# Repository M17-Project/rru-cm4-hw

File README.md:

[![CC BY-NC-SA 4.0][cc-by-nc-sa-shield]][cc-by-nc-sa]

# rru-cm4-hw
Remote Radio Unit - interface board

## License
This work is licensed under a
[Creative Commons Attribution-NonCommercial-ShareAlike 4.0 International License][cc-by-nc-sa].

[![CC BY-NC-SA 4.0][cc-by-nc-sa-image]][cc-by-nc-sa]

[cc-by-nc-sa]: http://creativecommons.org/licenses/by-nc-sa/4.0/
[cc-by-nc-sa-image]: https://licensebuttons.net/l/by-nc-sa/4.0/88x31.png
[cc-by-nc-sa-shield]: https://img.shields.io/badge/License-CC%20BY--NC--SA%204.0-lightgrey.svg

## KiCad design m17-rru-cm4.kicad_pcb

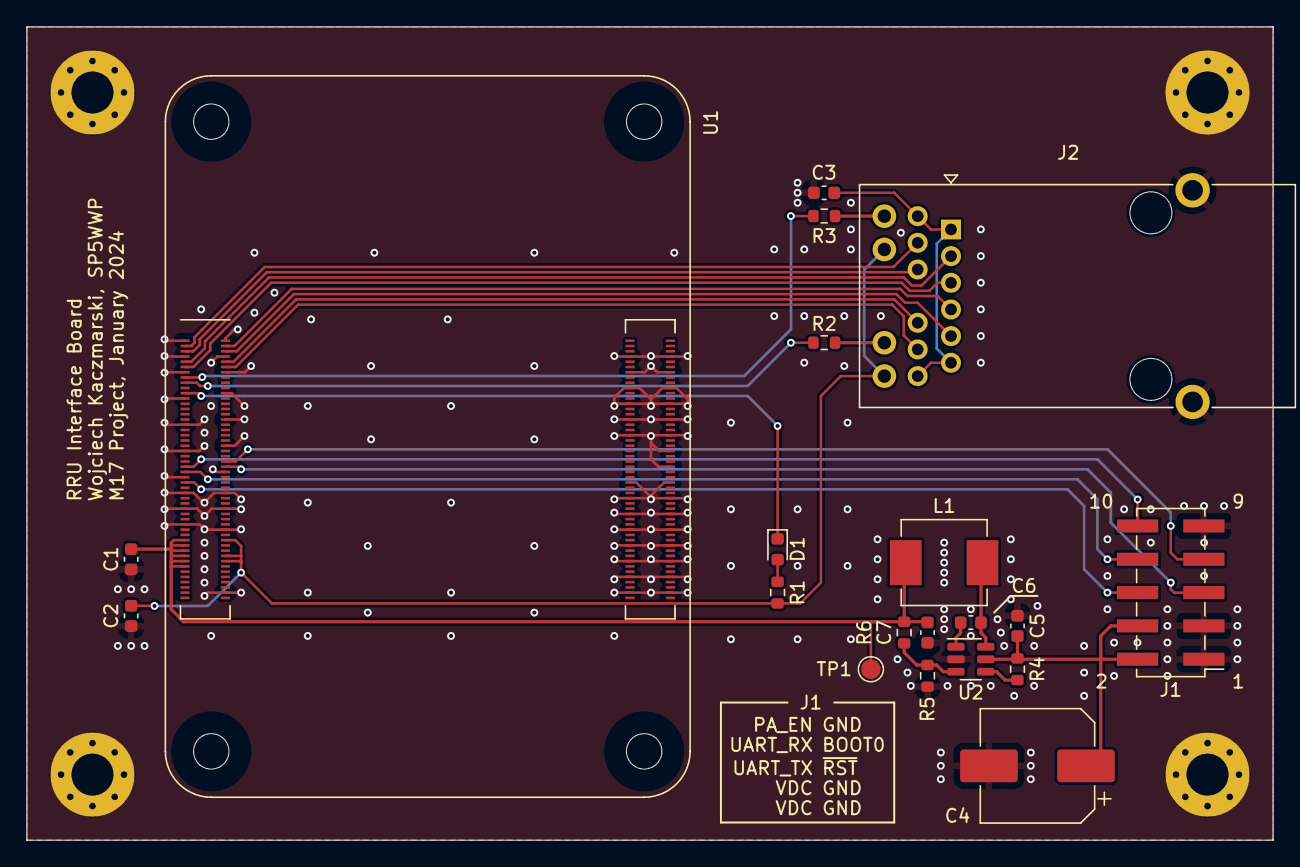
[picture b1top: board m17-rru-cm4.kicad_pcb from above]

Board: 2 copper layers, 95.0 x 62.0 mm, 24 parts (0 on the bottom side), 28 nets.

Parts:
C1, C2, C3, C5, C6: 100n; C_0603_1608Metric
C4: 100u/50V; CP_Elec_8x10.5
C7: 22u/6.3V; C_0603_1608Metric
D1: LED GRN; LED_0603_1608Metric
H1, H2, H3, H4: MountingHole_Pad; MountingHole_3.2mm_M3_Pad_Via
J1: Conn_02x05_Odd_Even; PinHeader_2x05_P2.54mm_Vertical_SMD
J2: RJ45_JK0654219; RJ45_Pulse_JK0654219NL_Horizontal
L1: 10u; L_Vishay_IHLP-2525
R1, R2, R3: 470R; R_0603_1608Metric
R4: 100k; R_0603_1608Metric
R5: 24k; R_0603_1608Metric
R6: 126k; R_0603_1608Metric
TP1: TP; TestPoint_Pad_D1.5mm
U1: Compute Module 4; Raspberry-Pi-4-Compute-Module
U2: TP6841; SOT-23-6

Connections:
+3.3V: C2.1, J2.14 (LED2+), J2.16 (LED1+), R1.1, U1.78 (GPIO_VREF), U1.84 (CM4_3.3V_Out), U1.86 (CM4_3.3V_Out)
/CM4 module/5V: C1.1, C7.2, L1.2, R6.2, TP1.1, U1.77 (+5V), U1.79 (+5V), U1.81 (+5V), U1.83 (+5V), U1.85 (+5V), U1.87 (+5V)
/CM4 module/BOOT0: J1.7, U1.48 (GPIO27)
/CM4 module/ETH_0N: J2.10 (MX1-), U1.10 (Ethernet_Pair0_N)
/CM4 module/ETH_0P: J2.11 (MX1+), U1.12 (Ethernet_Pair0_P)
/CM4 module/ETH_1N: J2.5 (MX2-), U1.6 (Ethernet_Pair1_N)
/CM4 module/ETH_1P: J2.4 (MX2+), U1.4 (Ethernet_Pair1_P)
/CM4 module/ETH_2N: J2.2 (MX3-), U1.9 (Ethernet_Pair2_N)
/CM4 module/ETH_2P: J2.3 (MX3+), U1.11 (Ethernet_Pair2_P)
/CM4 module/ETH_3N: J2.9 (MX4-), U1.5 (Ethernet_Pair3_N)
/CM4 module/ETH_3P: J2.8 (MX4+), U1.3 (Ethernet_Pair3_P)
/CM4 module/ETH_LEDG: R2.1, U1.17 (~Ethernet_nLED2)
/CM4 module/ETH_LEDY: R3.1, U1.15 (~Ethernet_nLED3)
/CM4 module/PA_EN: J1.10, U1.49 (GPIO18)
/CM4 module/UART_RX: J1.8, U1.51 (GPIO15)
/CM4 module/UART_TX: J1.6, U1.55 (GPIO14)
/CM4 module/~RST: J1.5, U1.50 (GPIO17)
/Interfaces/DC_SUPPLY: C4.1, C5.1, J1.2, J1.4, R4.1, U2.5 (VIN)
GND: C1.2, C2.2, C3.2, C4.2, C5.2, C7.1, H1.1, H2.1, H3.1, H4.1, J1.1, J1.3, J1.9, J2.SH, R5.2, U1.1 (GND), U1.2 (GND), U1.7 (GND), U1.8 (GND), U1.13 (GND), U1.14 (GND), U1.22 (GND), U1.23 (GND), U1.32 (GND), U1.33 (GND), U1.42 (GND), U1.43 (GND), U1.52 (GND), U1.53 (GND), U1.59 (GND), U1.60 (GND), U1.65 (GND), U1.66 (GND), U1.71 (GND), U1.74 (GND), U1.98 (GND), U1.107 (GND), U1.108 (GND), U1.113 (GND), U1.114 (GND), U1.119 (GND), U1.120 (GND), U1.125 (GND), U1.126 (GND), U1.131 (GND), U1.132 (GND), U1.137 (GND), U1.138 (GND), U1.144 (GND), U1.150 (GND), U1.155 (GND), U1.156 (GND), U1.161 (GND), U1.162 (GND), U1.167 (GND), U1.168 (GND), U1.173 (GND), U1.174 (GND), U1.179 (GND), U1.180 (GND), U1.185 (GND), U1.186 (GND), U1.191 (GND), U1.192 (GND), U1.197 (GND), U1.198 (GND), U2.2 (GND)
unnamed: D1.2 (A), R1.2
unnamed: D1.1 (K), U1.21 (~Pi_nLED_Activity)
unnamed: J2.15 (LED1-), R2.2
unnamed: J2.13 (LED2-), R3.2
unnamed: C3.1, J2.1 (MXCT3), J2.6 (MXCT2), J2.7 (MXCT4), J2.12 (MXCT1)
unnamed: C6.1, U2.1 (BST)
unnamed: R4.2, U2.4 (EN)
unnamed: R5.1, R6.1, U2.3 (FB)
unnamed: C6.2, L1.1, U2.6 (SW)

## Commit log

2024-01-22 init
2024-01-22 PN update, BOM
2024-01-22 WIP PCB
2024-01-22 NC pins
2024-01-23 WIP PCB layout
2024-01-23 silkscreen update
2024-01-23 BOM update
2024-01-23 missing comma
2024-01-24 pcb render
